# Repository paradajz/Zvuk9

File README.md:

# Zvuk9

Zvuk9 is an expressive USB MIDI controller used to play melodic instruments or drums / samples.

Zvuk9 features:

- 9 pressure and position sensitive pads
- Velocity sensitivity (3 levels of sensitivity and 3 velocity response curves)
- X and Y MIDI assignable to CC (CCs can be the same for all pads or unique per pad)
- X or Y can be set to send pitch bend instead of CC
- Aftertouch (channel or polyphonic)
- 15 programs for storing settings (scale, tonic, split status, X & Y controls, on/off status for notes, aftertouch, and X and Y)
- 7 predefined scales available: natural minor, harmonic minor, melodic minor, major, harmonic major, pentatonic minor, and pentatonic major
- 10 user scales available so you can set which pad will play which note or notes
- Chords can be assigned through user scales, a maximum of 7 notes can be assigned to a pad
- Tonic can be set with Notes buttons
- Notes buttons are illuminated, showing which notes are currently available and which note is currently playing
- By default, tonic goes on Pad1; by using Notes up/down function, all notes can be moved
- Encoder controls for X & Y: CC/Pitch bend, min, max, curve
- Total of 13 response curves available for X and Y
- 4 on/off buttons: notes, X, Y, and aftertouch
- In Split mode, all controls for X and Y, state of 4 on/off buttons, and MIDI channel are unique per pad
- Transport controls: play, stop, and record can be set to MCC, CC, or MCC+CC
- Note off type choice (off channel, on channel/0 velocity)
- All settings saved during reboot
- MIDI over USB and MIDI through 3.5mm mini jack out (cable mini jack to MIDI DIN included)
- Configurable MIDI running status for DIN MIDI
- OLED display

# Compiling

Several compile options are available:

 - Release - Standard firmware with USB MIDI support.
    - Command: `make fw_rls`
 - Debug - Uses LUFA virtual serial mode to print various messages during Zvuk9 usage (USB MIDI is disabled)
    - Command: `make fw_debug`
 - Bootloader - Used to compile bootloader which uses LUFA HID protocol
     - Command: `make boot`

Requirements:

- Linux (tested on Ubuntu 16.04)
- Make
- AVR toolchain
- srec_cat

# Firmware upload

Before uploading Zvuk9 firmware, controller must be put into firmware update mode. To do this, unplug controller from USB, press and hold small button located next to MIDI connector and connect USB cable to PC. After that, PC will recognize Zvuk9 as HID device. Once the bootloader is active, run `hid_bootloader_loader.exe` found under `/bin` directory. This tool will automatically write firwmare to Zvuk9. Make sure `FLASH.hex` is present in directory. Controller will automatically load new firmware once updating is finished.

# Licencing

Zvuk9 uses various modules which are licenced under different licenses. 

- LUFA is licenced under modified MIT licence.
- MIDI module is licenced under MIT.
- U8G2 is licenced under Two-clause BSD licence.
- Core and LESS-DB modules are available under MIT licence.

This project is available under GNU GPLv3 licence. For commerical uses commercial licence is available on demand.

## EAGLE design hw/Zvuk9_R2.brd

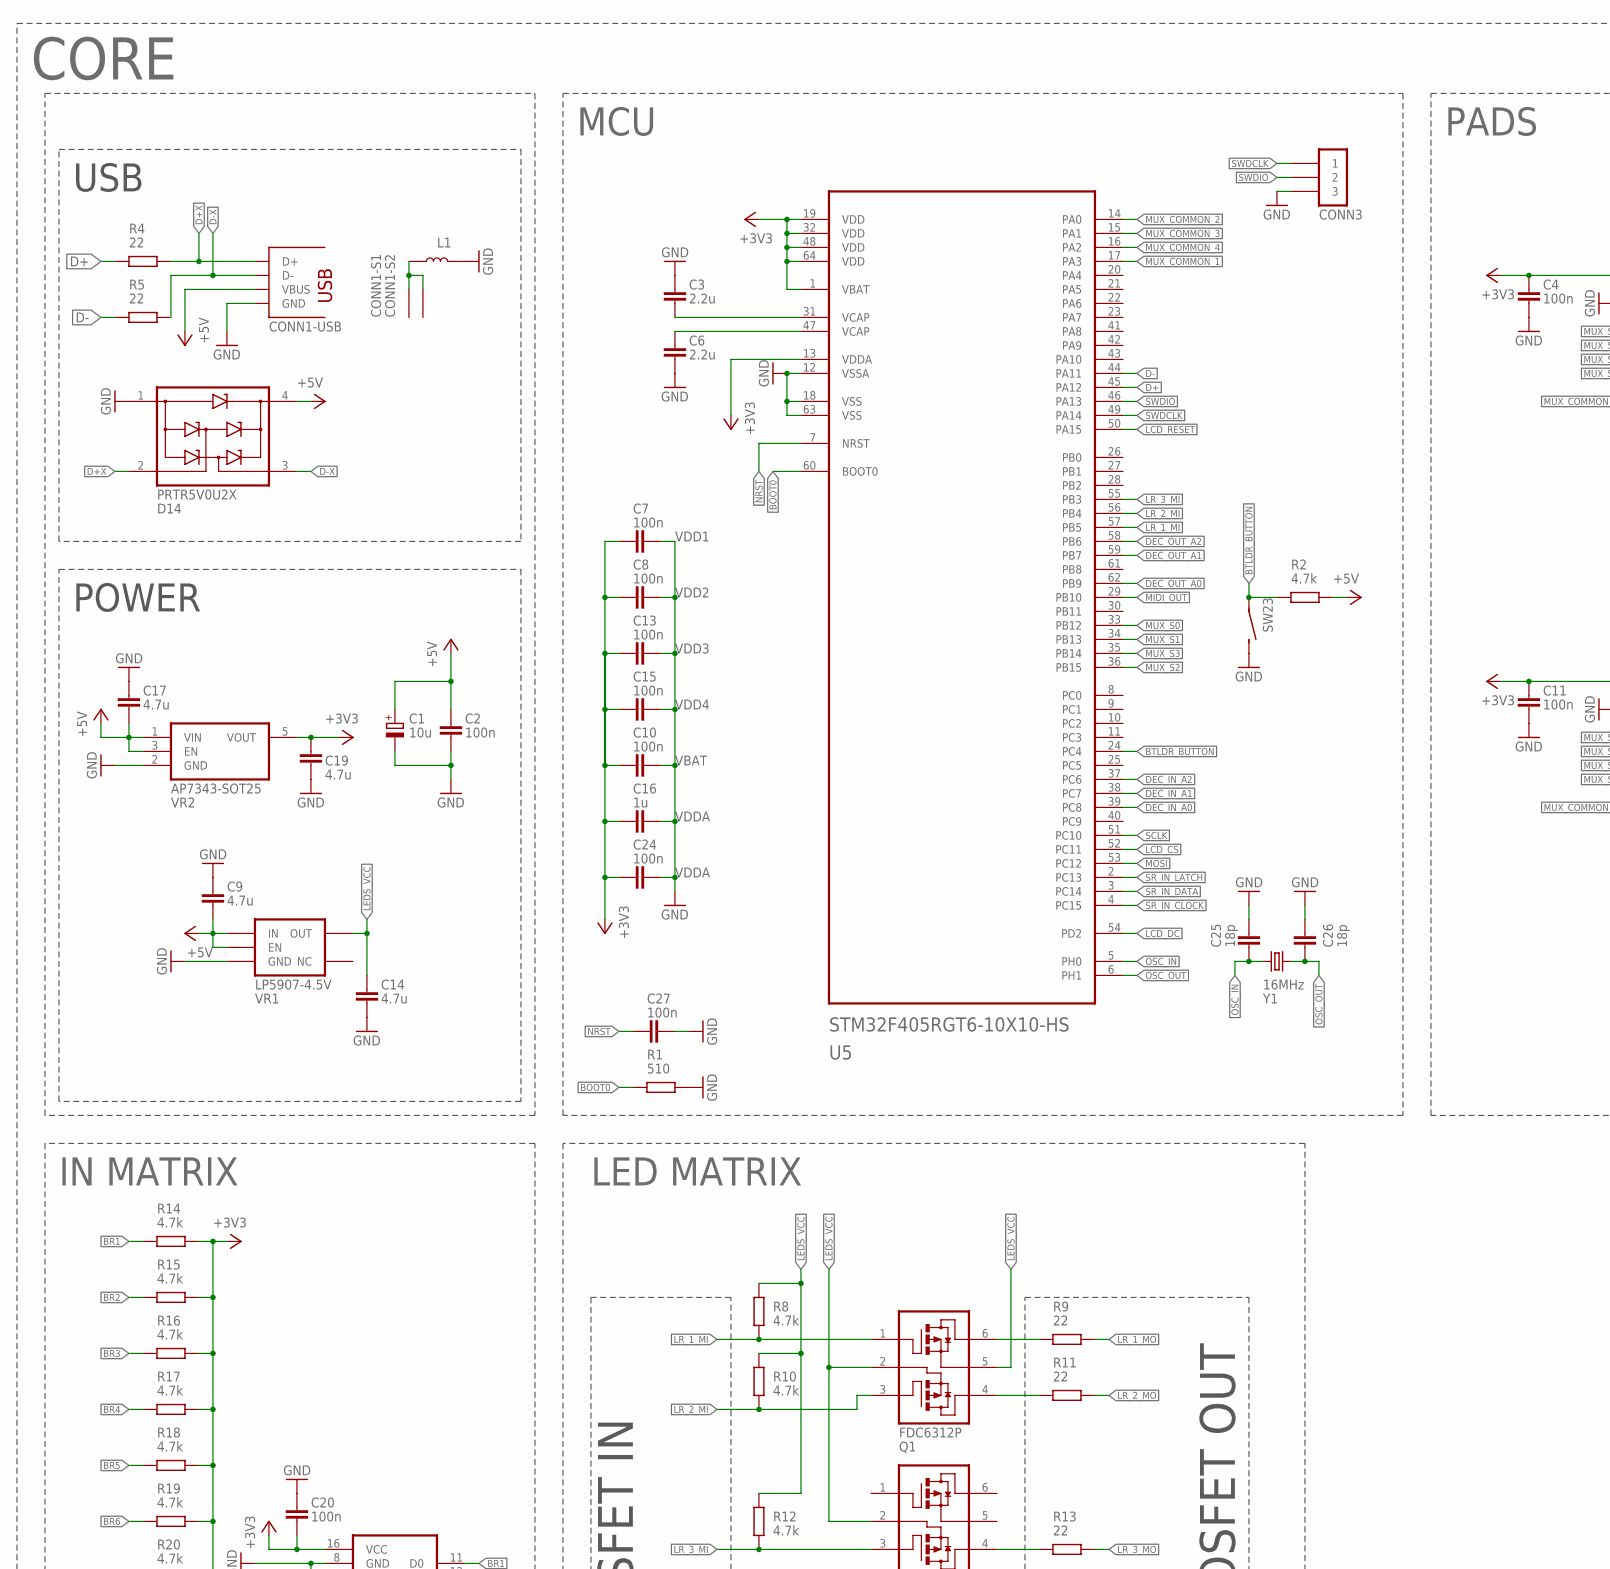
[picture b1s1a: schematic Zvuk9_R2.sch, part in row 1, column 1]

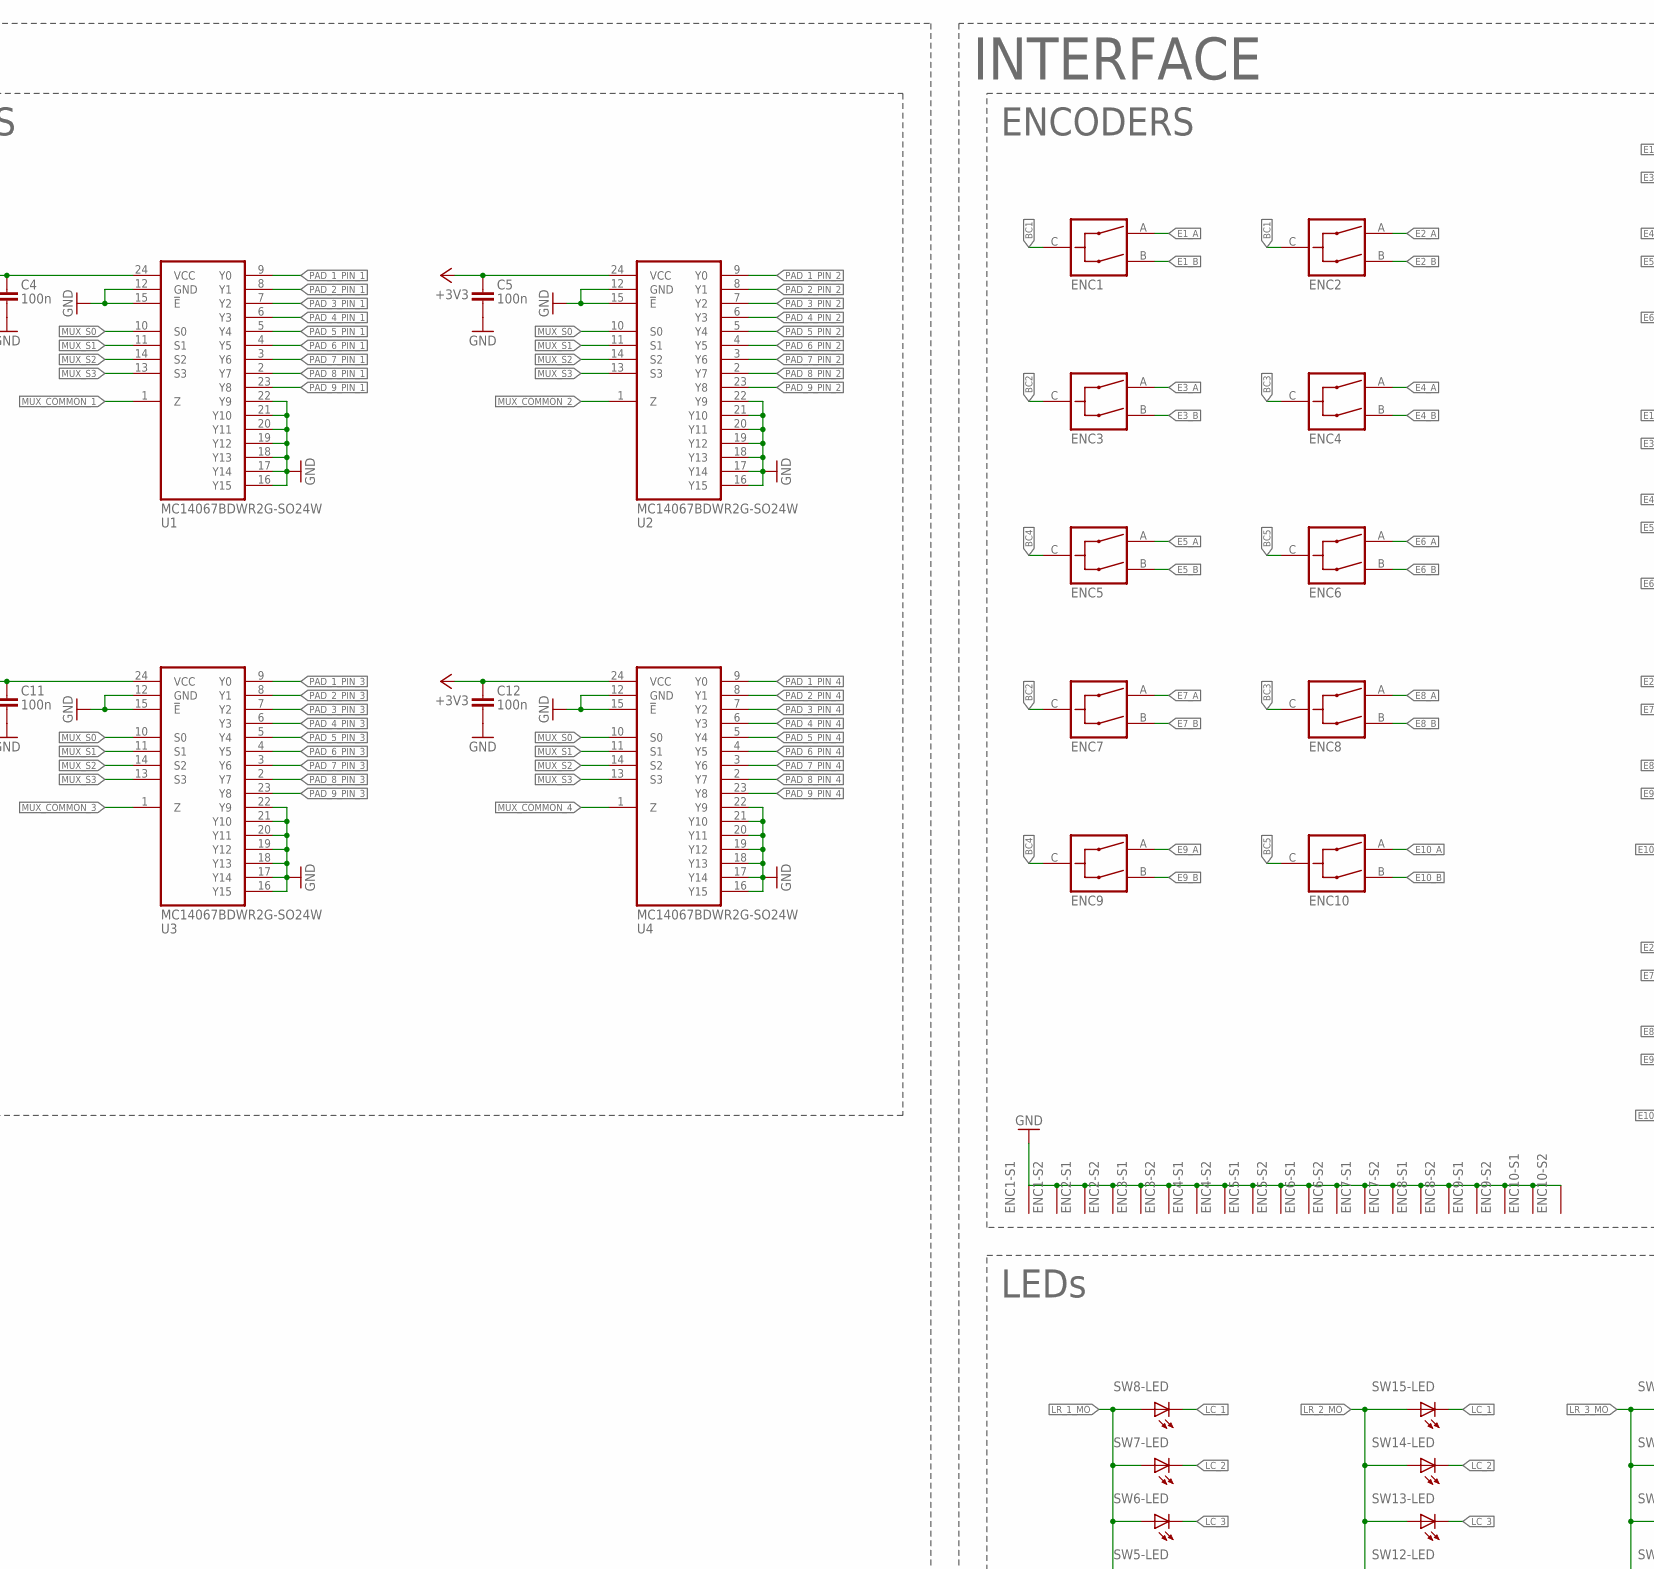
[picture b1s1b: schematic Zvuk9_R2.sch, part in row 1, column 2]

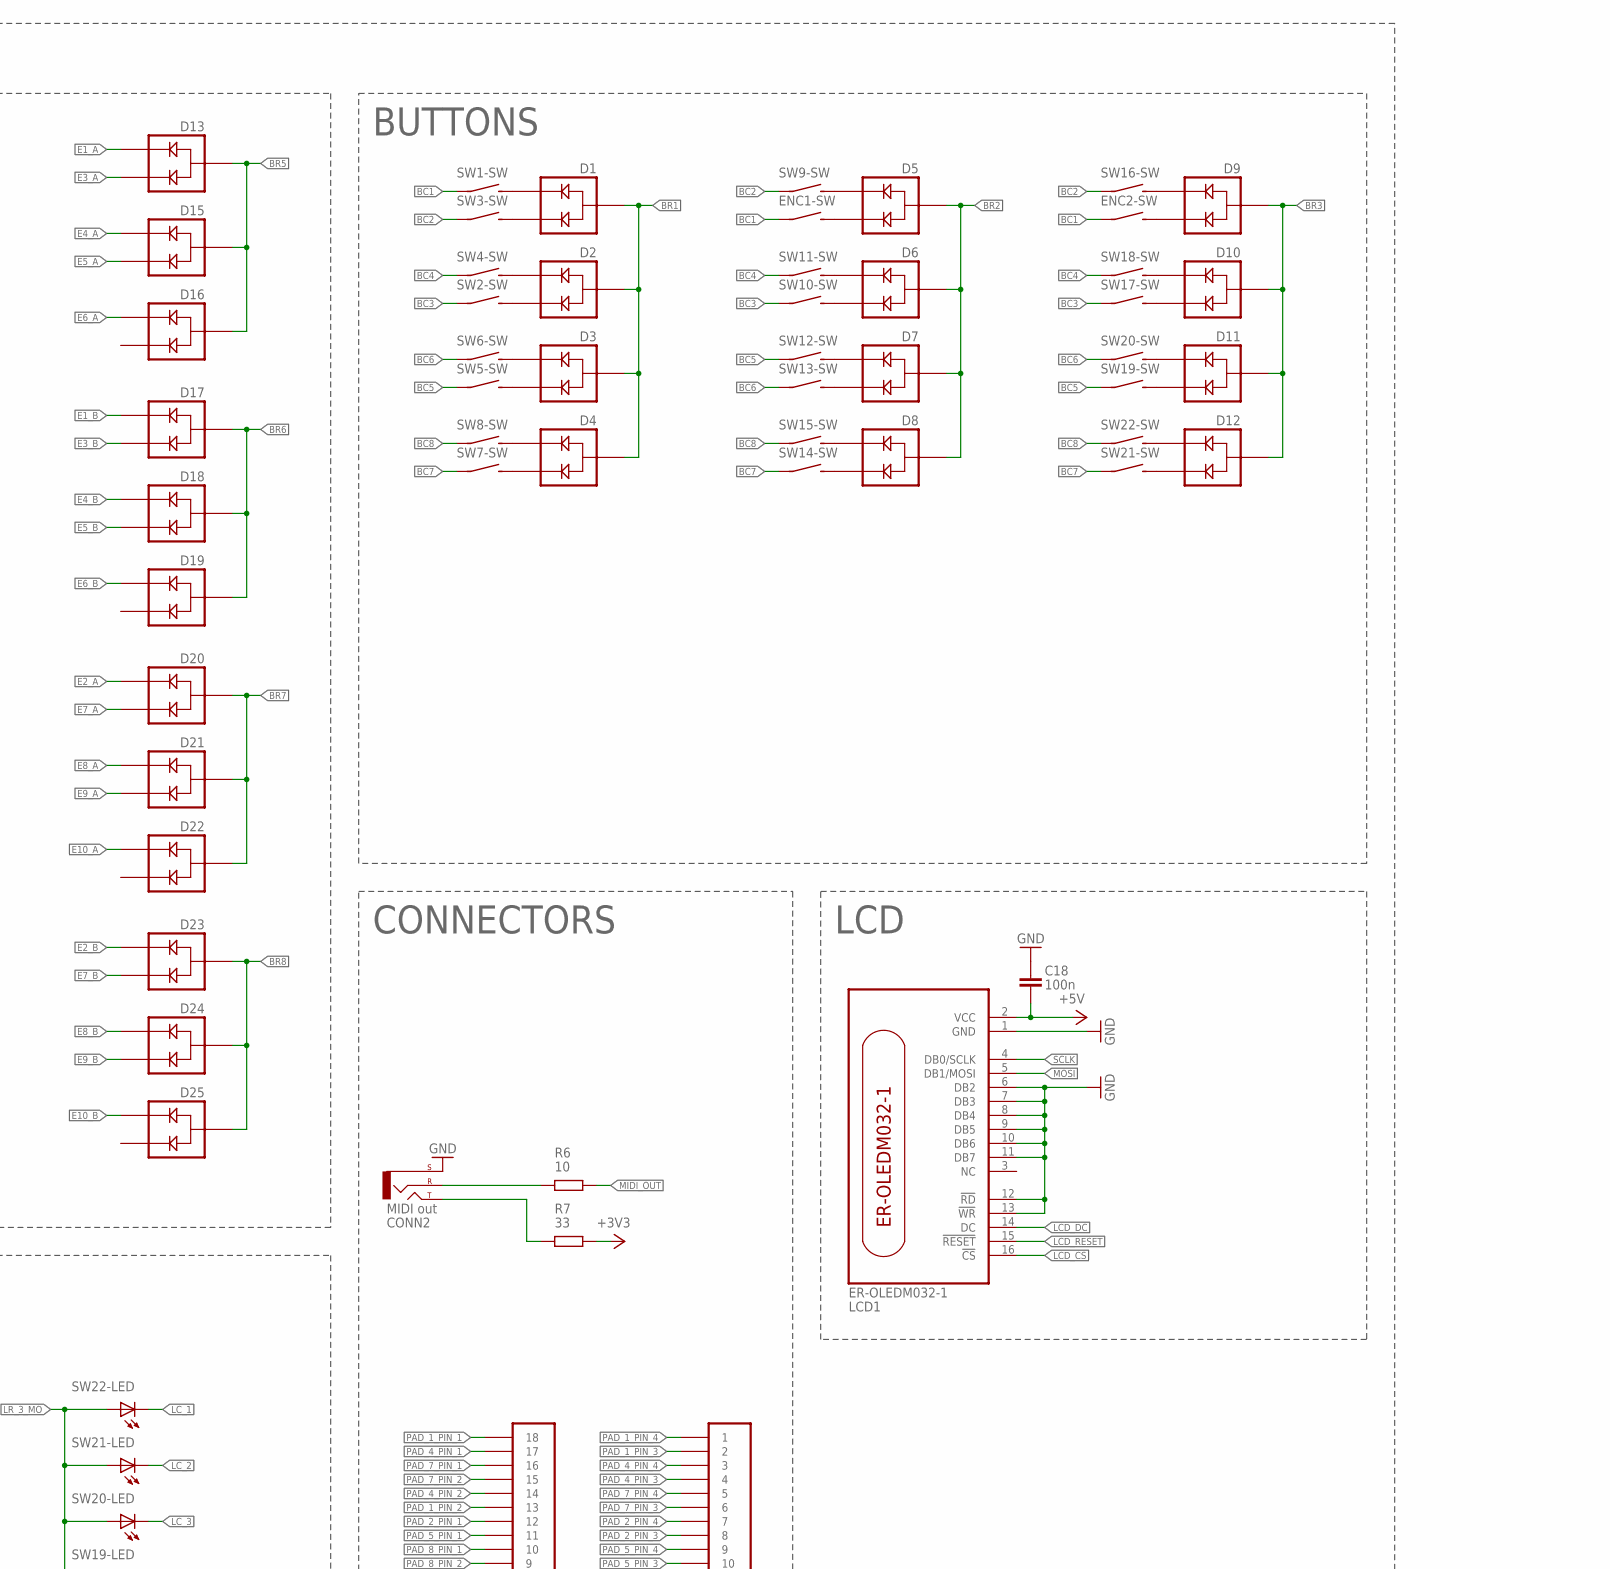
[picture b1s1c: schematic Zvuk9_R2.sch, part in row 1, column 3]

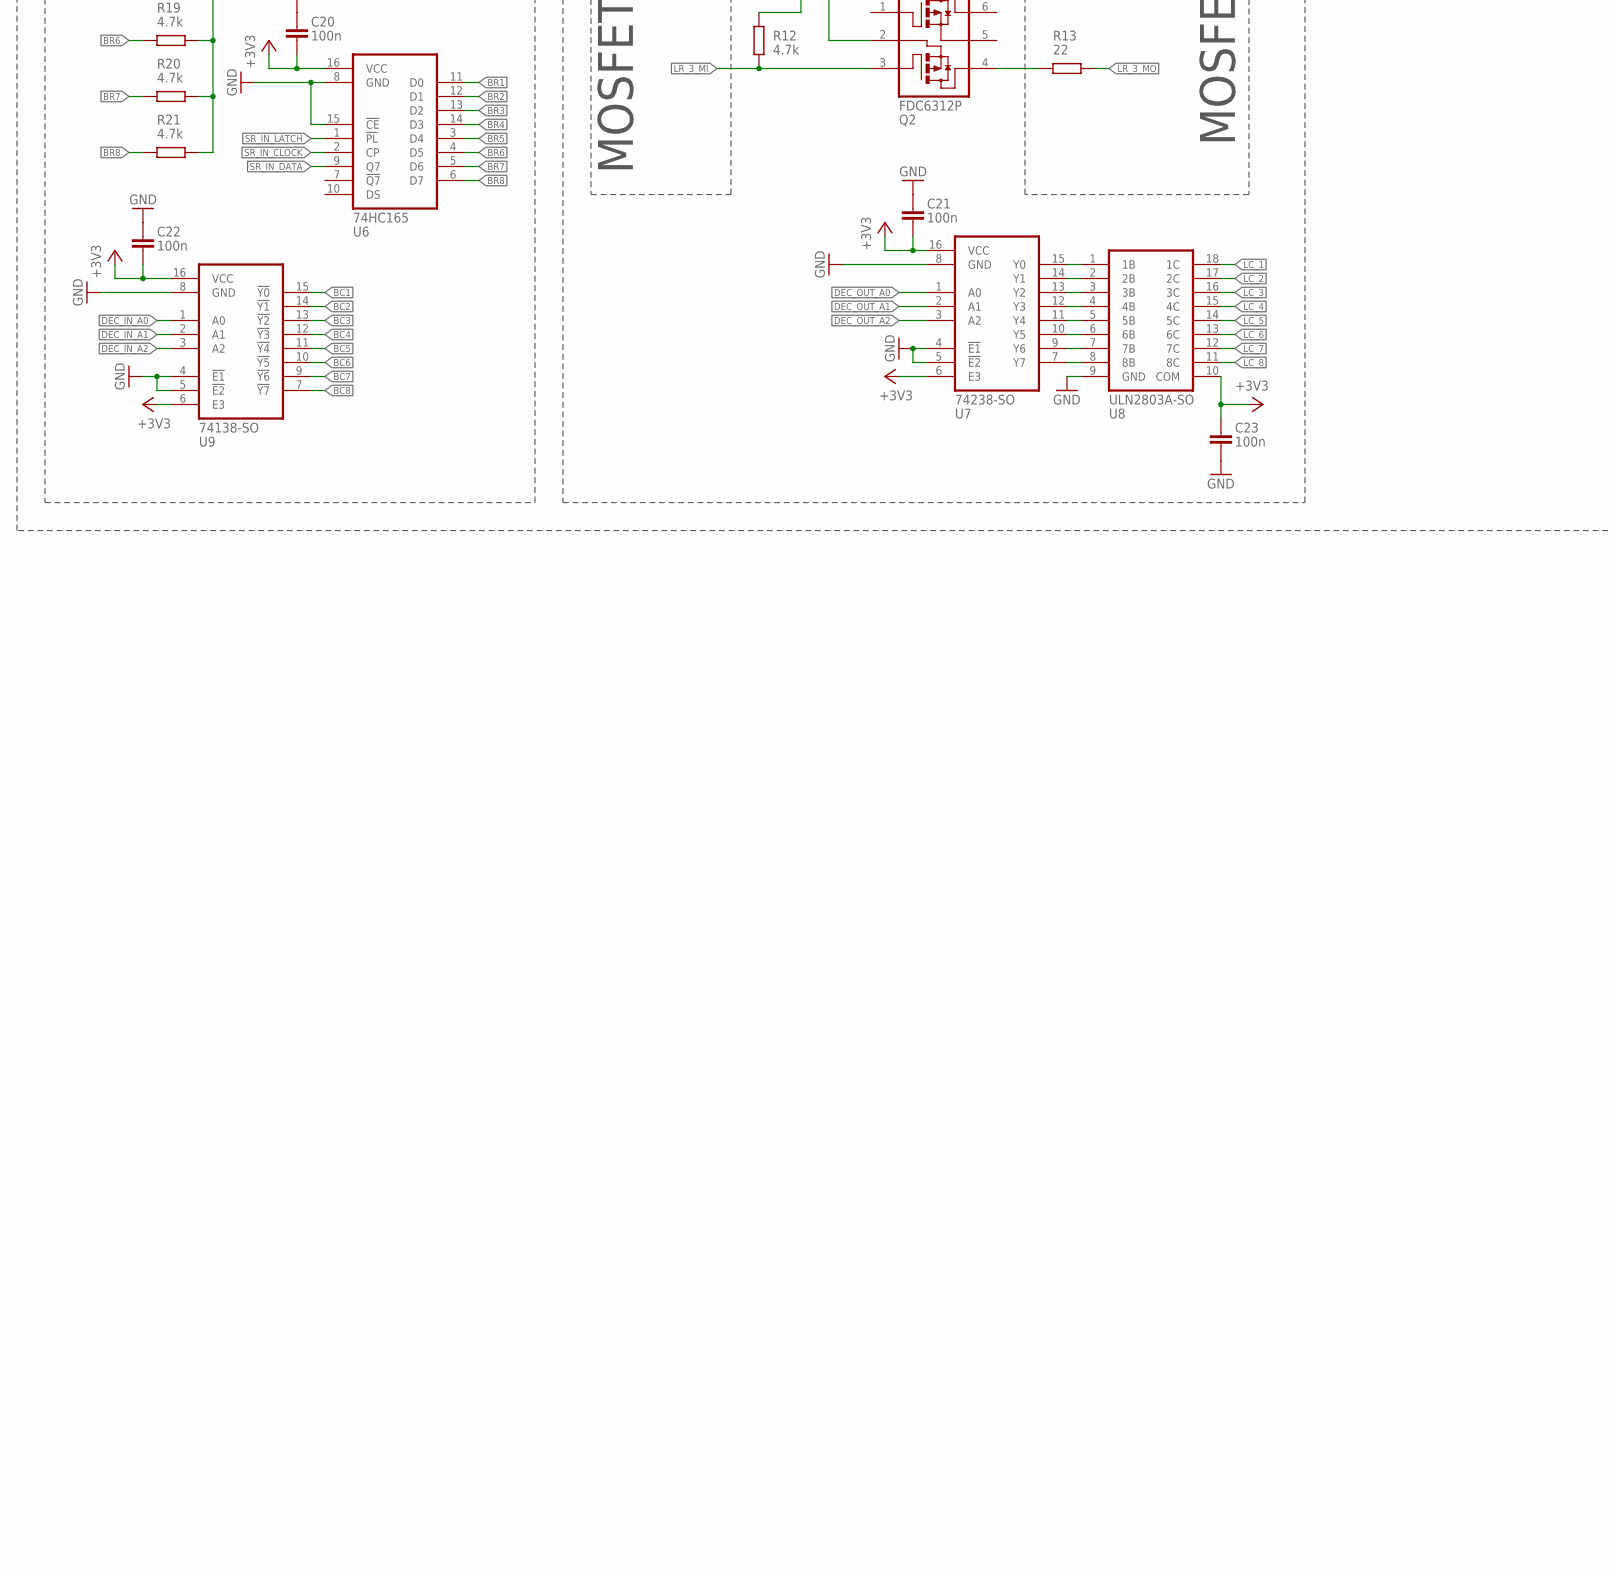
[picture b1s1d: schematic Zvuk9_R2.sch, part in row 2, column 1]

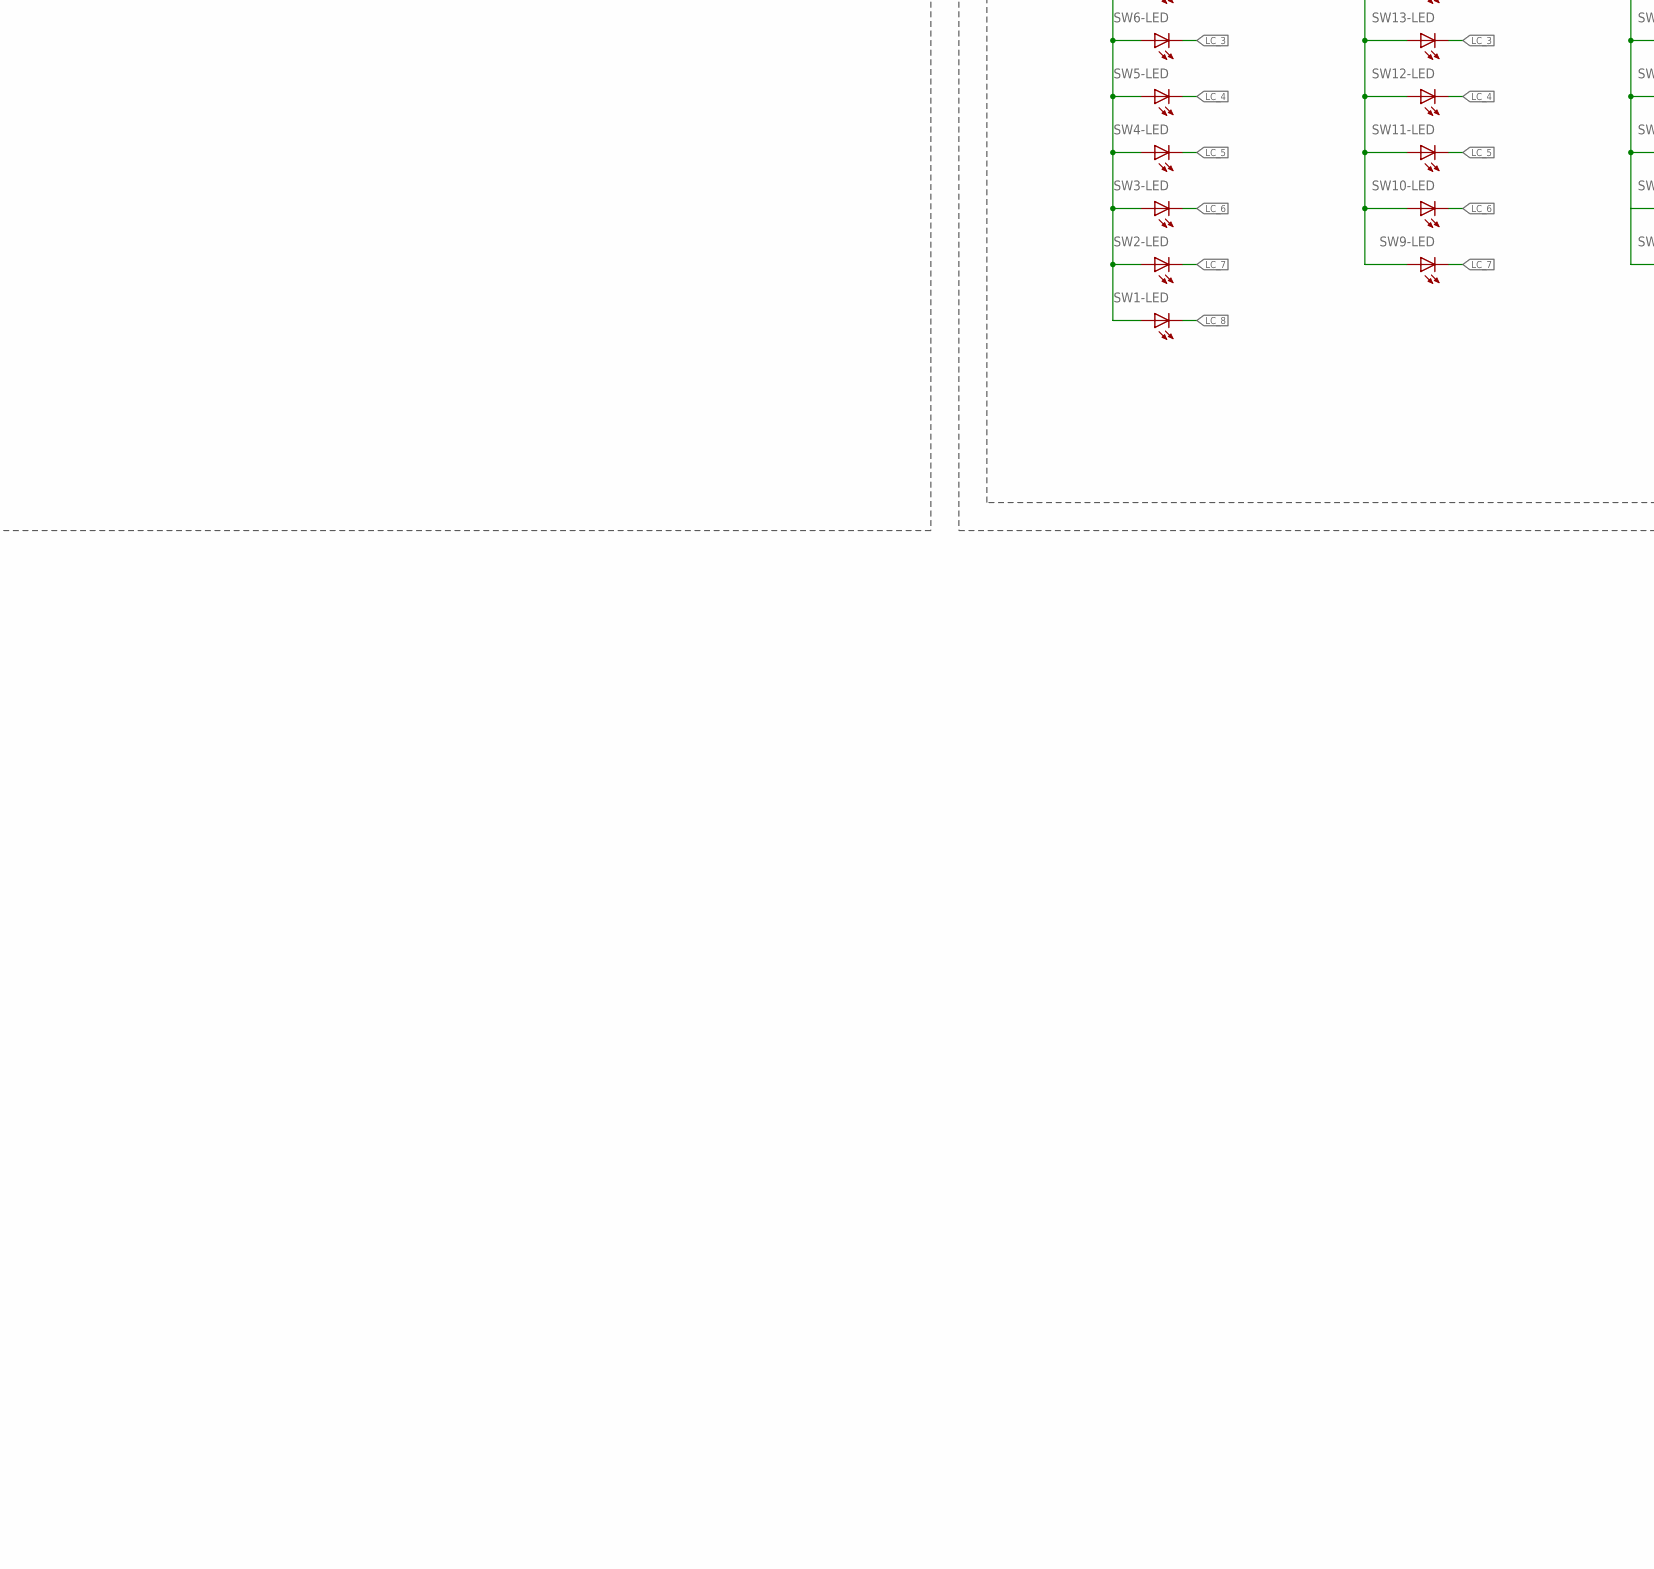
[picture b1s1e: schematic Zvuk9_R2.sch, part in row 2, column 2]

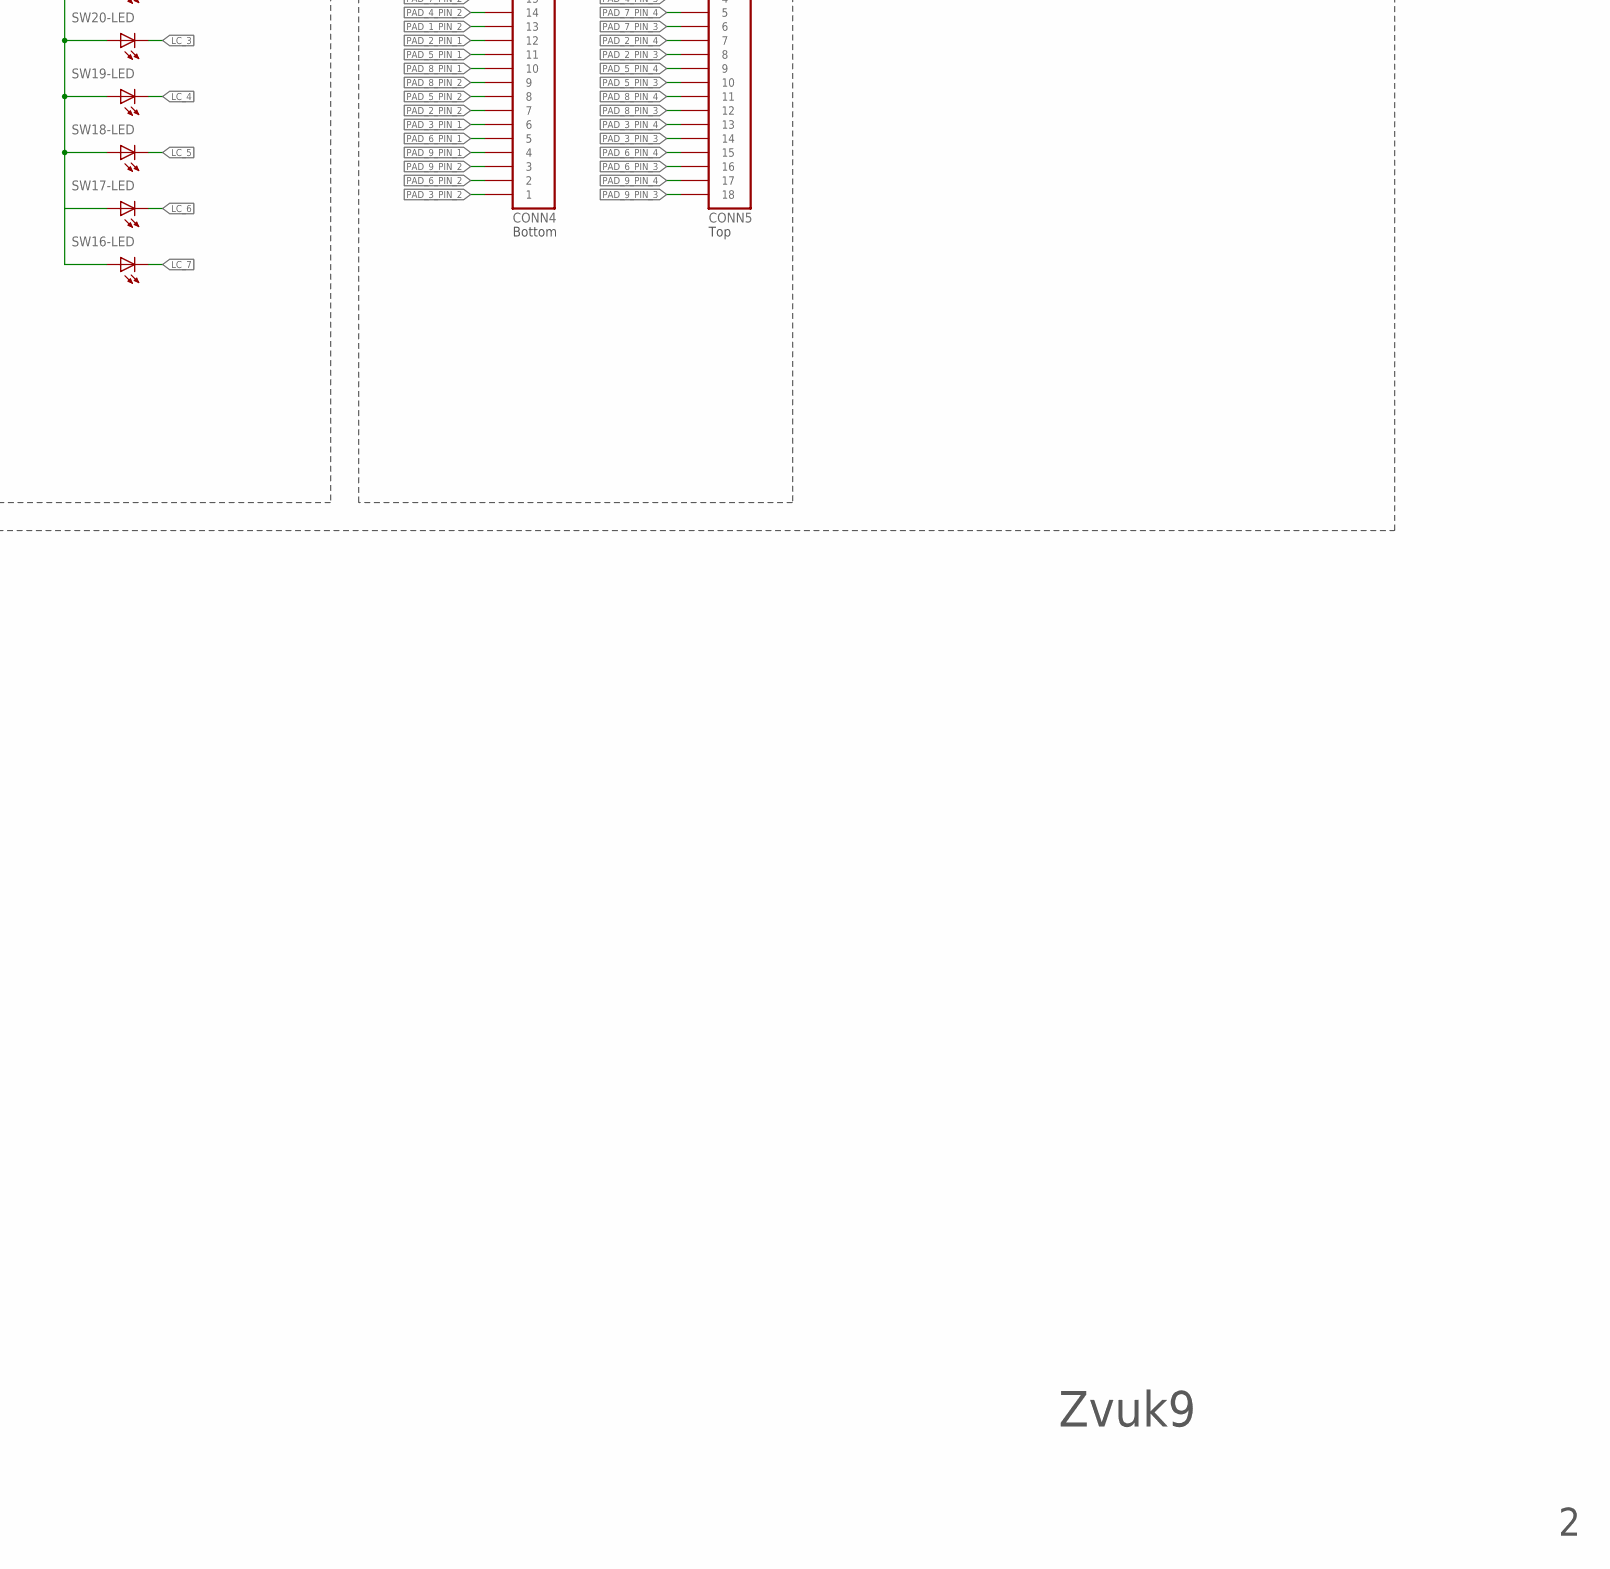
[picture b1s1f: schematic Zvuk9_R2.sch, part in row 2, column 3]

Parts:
C1: 10u; C-TH-E-0502
C2, C4, C5, C7, C8, C10, C11, C12, C13, C15, C18, C20, C21, C22, C23, C24, C27: 100n; C0805
C3, C6: 2.2u; C0805
C9, C14, C17, C19: 4.7u; C0805
C16: 1u; C0805
C25, C26: 18p; C0805
CONN1: USB-B-H; USB-B-PTH
CONN2: MIDI out; SJ1-3523N
CONN3: PINHD-1X03-TH-2.54MM; 1X03-2.54-V
CONN4, CONN5: PINHD-1X18-FFC-SMD-1MM; MOLEX-52271-1879
D1, D2, D3, D4, D5, D6, D7, D8, D9, D10, D11, D12, D13, D15, D16, D17, D18, D19, D20, D21, D22, D23, D24, D25: BAW56; SOT23
D14: PRTR5V0U2X; SOT143
ENC1, ENC2: ALPS-EC12D1524403; ALPS_EC12-SW
ENC3, ENC4, ENC5, ENC6, ENC7, ENC8, ENC9, ENC10: ALPS-EC12E24404AX; EC12E-1
L1: FERRITE_BEAD-BLM21PG221SN1D; L0805
LCD1: ER-OLEDM032-1; ER-OLEDM032-W
Q1, Q2: FDC6312P; SSOT6
R1: 510; R0805
R2, R8, R10, R12, R14, R15, R16, R17, R18, R19, R20, R21: 4.7k; R0805
R4, R5, R9, R11, R13: 22; R0805
R6: 10; R0805
R7: 33; R0805
SW1, SW2, SW3, SW4, SW5, SW6, SW7, SW8, SW9, SW10, SW11, SW12, SW13, SW14, SW15, SW16, SW17, SW18, SW19, SW20, SW21, SW22: OMRON-B3W-9
SW23: SWITCH-B3F; B3F-312X
U1, U2, U3, U4: MC14067BDWR2G-SO24W; SO24-W
U5: STM32F405RGT6-10X10-HS; TQFP-64-10X10-HS
U6: 74HC165; SO16
U7: 74238-SO; SO16
U8: ULN2803A-SO; SO18
U9: 74138-SO; SO16
VR1: LP5907-4.5V; SOT23-5
VR2: AP7343-SOT25; SOT25
Y1: 16MHz; HC49US

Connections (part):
+3V3: C4.1, C5.1, C7.1, C8.1, C10.1, C11.1, C12.1, C13.1, C15.1, C16.1, C19.1, C20.2, C21.2, C22.2, C23.1, C24.1, R7.2, R14.2, R15.2, R16.2, R17.2, R18.2, R19.2, R20.2, R21.2, U1.24 (VCC), U2.24 (VCC), U3.24 (VCC), U4.24 (VCC), U5.1 (VBAT), U5.13 (VDDA), U5.19 (VDD), U5.32 (VDD), U5.48 (VDD), U5.64 (VDD), U6.16 (VCC), U7.6 (E3), U7.16 (VCC), U8.10 (COM), U9.6 (E3), U9.16 (VCC), VR2.5 (VOUT)
+5V: C1.+, C2.1, C9.2, C17.2, C18.2, CONN1.VBUS, D14.4 (VCC), LCD1.2 (VCC), R2.2, VR1.1 (IN), VR1.3 (EN), VR2.1 (VIN), VR2.3 (EN)
BC1: ENC1.C, ENC1.D (1), ENC2.C, ENC2.D (1), SW1.1, U9.15 (!Y0)
BC2: ENC3.C, ENC7.C, SW3.1, SW9.1, SW16.1, U9.14 (!Y1)
BC3: ENC4.C, ENC8.C, SW2.1, SW10.1, SW17.1, U9.13 (!Y2)
BC4: ENC5.C, ENC9.C, SW4.1, SW11.1, SW18.1, U9.12 (!Y3)
BC5: ENC6.C, ENC10.C, SW5.1, SW12.1, SW19.1, U9.11 (!Y4)
BC6: SW6.1, SW13.1, SW20.1, U9.10 (!Y5)
BC7: SW7.1, SW14.1, SW21.1, U9.9 (!Y6)
BC8: SW8.1, SW15.1, SW22.1, U9.7 (!Y7)
BOOT0: R1.1, U5.60 (BOOT0)
BR1: D1.3, D2.3, D3.3, D4.3, R14.1, U6.11 (D0)
BR2: D5.3, D6.3, D7.3, D8.3, R15.1, U6.12 (D1)
BR3: D9.3, D10.3, D11.3, D12.3, R16.1, U6.13 (D2)
BR4: R17.1, U6.14 (D3)
BR5: D13.3, D15.3, D16.3, R18.1, U6.3 (D4)
BR6: D17.3, D18.3, D19.3, R19.1, U6.4 (D5)
BR7: D20.3, D21.3, D22.3, R20.1, U6.5 (D6)
BR8: D23.3, D24.3, D25.3, R21.1, U6.6 (D7)
BTLDR_BUTTON: R2.1, SW23.1, U5.24 (PC4)
D+: R4.1, U5.45 (PA12)
D+X: CONN1.D+, D14.2 (I/O1), R4.2
D-: R5.1, U5.44 (PA11)
D-X: CONN1.D-, D14.3 (I/O2), R5.2
DEC_IN_A0: U5.39 (PC8), U9.1 (A0)
DEC_IN_A1: U5.38 (PC7), U9.2 (A1)
DEC_IN_A2: U5.37 (PC6), U9.3 (A2)
DEC_OUT_A0: U5.62 (PB9), U7.1 (A0)
DEC_OUT_A1: U5.59 (PB7), U7.2 (A1)
DEC_OUT_A2: U5.58 (PB6), U7.3 (A2)
E1_A: D13.1, ENC1.A
E1_B: D17.1, ENC1.B
E2_A: D20.1, ENC2.A
E2_B: D23.1, ENC2.B
E3_A: D13.2, ENC3.A
E3_B: D17.2, ENC3.B
E4_A: D15.1, ENC4.A
E4_B: D18.1, ENC4.B
E5_A: D15.2, ENC5.A
E5_B: D18.2, ENC5.B
E6_A: D16.1, ENC6.A
E6_B: D19.1, ENC6.B
E7_A: D20.2, ENC7.A
E7_B: D23.2, ENC7.B
E8_A: D21.1, ENC8.A
E8_B: D24.1, ENC8.B
E9_A: D21.2, ENC9.A
E9_B: D24.2, ENC9.B
E10_A: D22.1, ENC10.A
E10_B: D25.1, ENC10.B
GND: C1.-, C2.2, C3.1, C4.2, C5.2, C6.2, C7.2, C8.2, C9.1, C10.2, C11.2, C12.2, C13.2, C14.2, C15.2, C16.2, C17.1, C18.1, C19.2, C20.1, C21.1, C22.1, C23.2, C24.2, C25.2, C26.2, C27.2, CONN1.GND, CONN2.1 (SLEEVE), CONN3.3, D14.1 (GND), ENC1.S1 (S), ENC1.S2 (S), ENC2.S1 (S), ENC2.S2 (S), ENC3.S1 (S), ENC3.S2 (S), ENC4.S1 (S), ENC4.S2 (S), ENC5.S1 (S), ENC5.S2 (S), ENC6.S1 (S), ENC6.S2 (S), ENC7.S1 (S), ENC7.S2 (S), ENC8.S1 (S), ENC8.S2 (S), ENC9.S1 (S), ENC9.S2 (S), ENC10.S1 (S), ENC10.S2 (S), L1.2, LCD1.1 (GND), LCD1.6 (DB2), LCD1.7 (DB3), LCD1.8 (DB4), LCD1.9 (DB5), LCD1.10 (DB6), LCD1.11 (DB7), LCD1.12 (!RD), LCD1.13 (!WR), R1.2, SW23.2, U1.12 (GND), U1.15 (!E), U1.16 (Y15), U1.17 (Y14), U1.18 (Y13), U1.19 (Y12), U1.20 (Y11), U1.21 (Y10), U1.22 (Y9), U2.12 (GND), U2.15 (!E), U2.16 (Y15), U2.17 (Y14), U2.18 (Y13), U2.19 (Y12), U2.20 (Y11), U2.21 (Y10)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
LCD_CS: LCD1.16 (!CS), U5.52 (PC11)
LCD_DC: LCD1.14 (DC), U5.54 (PD2)
LCD_RESET: LCD1.15 (!RESET), U5.50 (PA15)
LC_1: SW8.6-C (C), SW15.6-C (C), SW22.6-C (C), U8.18 (1C)
LC_2: SW7.6-C (C), SW14.6-C (C), SW21.6-C (C), U8.17 (2C)
LC_3: SW6.6-C (C), SW13.6-C (C), SW20.6-C (C), U8.16 (3C)
LC_4: SW5.6-C (C), SW12.6-C (C), SW19.6-C (C), U8.15 (4C)
LC_5: SW4.6-C (C), SW11.6-C (C), SW18.6-C (C), U8.14 (5C)
LC_6: SW3.6-C (C), SW10.6-C (C), SW17.6-C (C), U8.13 (6C)
LC_7: SW2.6-C (C), SW9.6-C (C), SW16.6-C (C), U8.12 (7C)
LC_8: SW1.6-C (C), U8.11 (8C)
LEDS_VCC: C14.1, Q1.2 (S2), Q1.5 (S1), Q2.2 (S2), R8.1, R10.1, R12.1, VR1.5 (OUT)
LR_1_MI: Q1.1 (G1), R8.2, U5.57 (PB5)
LR_1_MO: R9.2, SW1.6-A (A), SW2.6-A (A), SW3.6-A (A), SW4.6-A (A), SW5.6-A (A), SW6.6-A (A), SW7.6-A (A), SW8.6-A (A)
LR_2_MI: Q1.3 (G2), R10.2, U5.56 (PB4)
LR_2_MO: R11.2, SW9.6-A (A), SW10.6-A (A), SW11.6-A (A), SW12.6-A (A), SW13.6-A (A), SW14.6-A (A), SW15.6-A (A)
LR_3_MI: Q2.3 (G2), R12.2, U5.55 (PB3)
LR_3_MO: R13.2, SW16.6-A (A), SW17.6-A (A), SW18.6-A (A), SW19.6-A (A), SW20.6-A (A), SW21.6-A (A), SW22.6-A (A)
MIDI_OUT: R6.2, U5.29 (PB10)
MOSI: LCD1.5 (DB1/MOSI), U5.53 (PC12)
MUX_COMMON_1: U1.1 (Z), U5.17 (PA3)
MUX_COMMON_2: U2.1 (Z), U5.14 (PA0)
MUX_COMMON_3: U3.1 (Z), U5.15 (PA1)
MUX_COMMON_4: U4.1 (Z), U5.16 (PA2)
MUX_S0: U1.10 (S0), U2.10 (S0), U3.10 (S0), U4.10 (S0), U5.33 (PB12)
MUX_S1: U1.11 (S1), U2.11 (S1), U3.11 (S1), U4.11 (S1), U5.34 (PB13)
MUX_S2: U1.14 (S2), U2.14 (S2), U3.14 (S2), U4.14 (S2), U5.36 (PB15)
MUX_S3: U1.13 (S3), U2.13 (S3), U3.13 (S3), U4.13 (S3), U5.35 (PB14)
unnamed: U7.15 (Y0), U8.1 (1B)
unnamed: U7.14 (Y1), U8.2 (2B)
unnamed: U7.13 (Y2), U8.3 (3B)
unnamed: U7.12 (Y3), U8.4 (4B)
unnamed: D1.1, SW1.3 (2)
unnamed: D2.2, SW2.3 (2)
unnamed: CONN2.2 (TIP), R7.1
unnamed: D2.1, SW4.3 (2)
unnamed: D1.2, SW3.3 (2)
unnamed: D3.2, SW5.3 (2)
unnamed: D3.1, SW6.3 (2)
unnamed: C3.2, U5.31 (VCAP)
unnamed: C6.1, U5.47 (VCAP)
unnamed: D4.2, SW7.3 (2)
unnamed: D4.1, SW8.3 (2)
unnamed: D5.2, ENC1.E (2)
unnamed: D6.2, SW10.3 (2)
unnamed: D6.1, SW11.3 (2)
unnamed: D7.1, SW12.3 (2)
unnamed: D7.2, SW13.3 (2)
unnamed: D8.2, SW14.3 (2)
unnamed: D8.1, SW15.3 (2)
unnamed: D5.1, SW9.3 (2)
unnamed: D9.2, ENC2.E (2)
unnamed: D9.1, SW16.3 (2)
unnamed: D10.2, SW17.3 (2)
unnamed: D10.1, SW18.3 (2)
unnamed: D11.2, SW19.3 (2)
unnamed: D11.1, SW20.3 (2)
unnamed: D12.2, SW21.3 (2)
unnamed: D12.1, SW22.3 (2)
unnamed: CONN2.3 (RING), R6.1
unnamed: U7.11 (Y4), U8.5 (5B)
unnamed: U7.10 (Y5), U8.6 (6B)
unnamed: U7.9 (Y6), U8.7 (7B)
unnamed: U7.7 (Y7), U8.8 (8B)
unnamed: Q1.6 (D1), R9.1
unnamed: Q1.4 (D2), R11.1
unnamed: Q2.4 (D2), R13.1
NRST: C27.1, U5.7 (NRST)
OSC_IN: C25.1, U5.5 (PH0), Y1.1
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
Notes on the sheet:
LCD
BUTTONS
ENCODERS
CONNECTORS
Zvuk9
LEDs
USB
MOSFET IN
MOSFET OUT
MCU
POWER
IN MATRIX
LED MATRIX
CORE
INTERFACE
PADS
Bottom
Top
VBAT
VDD1
VDD2
VDD3
VDD4
VDDA

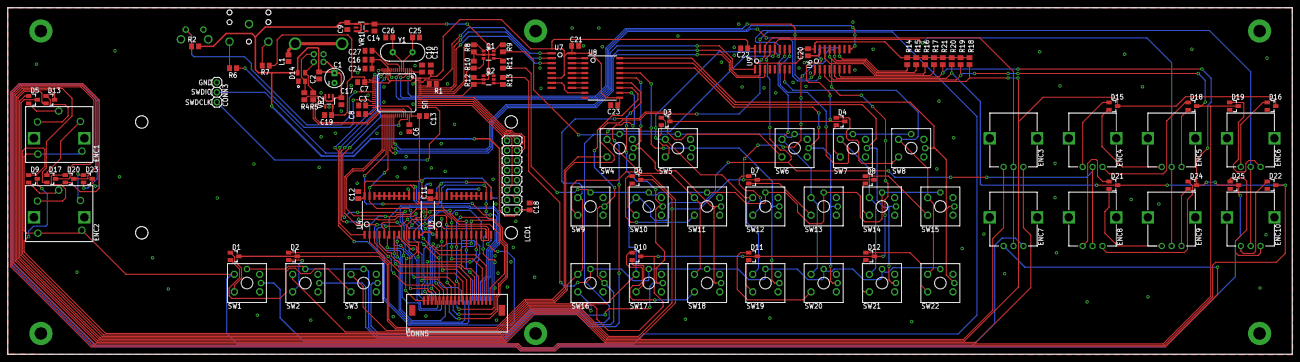
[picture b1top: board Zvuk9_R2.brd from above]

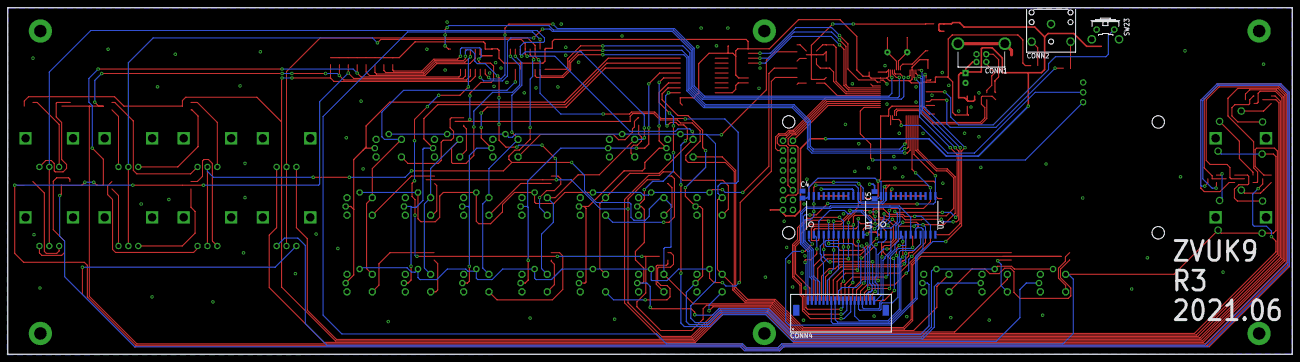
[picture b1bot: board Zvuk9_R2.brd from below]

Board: 2 copper layers, 330.1 x 89.0 mm, 126 parts (8 on the bottom side), 164 nets.

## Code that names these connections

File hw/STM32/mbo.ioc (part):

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Mcu.Name=STM32F410C(8-B)Tx
Mcu.Package=LQFP48
Mcu.UserName=STM32F410CBTx
PA0-WKUP.GPIOParameters=GPIO_Label
PA0-WKUP.GPIO_Label=LED_COL_DEC_1
PA0-WKUP.Signal=GPIO_Output
PA1.GPIOParameters=GPIO_Label
PA1.GPIO_Label=LED_COL_DEC_2
PA1.Signal=GPIO_Output
PA10.Mode=Asynchronous
PA10.Signal=USART1_RX
PA11.GPIOParameters=GPIO_Label
PA11.GPIO_Label=IN_MATRIX_COL_S2
PA11.Signal=GPIO_Output
PA12.GPIOParameters=GPIO_Label
PA12.GPIO_Label=IN_MATRIX_COL_S1
PA12.Signal=GPIO_Output
PA13.Mode=Serial_Wire
PA13.Signal=SYS_JTMS-SWDIO
PA14.Mode=Serial_Wire
PA14.Signal=SYS_JTCK-SWCLK
PA15.GPIOParameters=GPIO_Label
PA15.GPIO_Label=DISPLAY NSS
PA15.Mode=NSS_Signal_Hard_Output
PA15.Signal=SPI1_NSS
PA2.GPIOParameters=GPIO_Label
PA2.GPIO_Label=LED_COL_DEC_3
PA2.Signal=GPIO_Output
PA3.GPIOParameters=GPIO_Label
PA3.GPIO_Label=MUX COMMON 1
PA3.Signal=ADCx_IN3
PA4.GPIOParameters=GPIO_Label
PA4.GPIO_Label=MUX COMMON 2
PA4.Signal=ADCx_IN4
PA5.GPIOParameters=GPIO_Label
PA5.GPIO_Label=MUX COMMON 3
PA5.Signal=ADCx_IN5
PA6.GPIOParameters=GPIO_Label
PA6.GPIO_Label=MUX COMMON 4
PA6.Signal=ADCx_IN6
PA7.GPIOParameters=GPIO_Label
PA7.GPIO_Label=MUX S0
PA7.Signal=GPIO_Output
PA8.GPIOParameters=GPIO_Label
PA8.GPIO_Label=IN_MATRIX_COL_S0
PA8.Signal=GPIO_Output
PA9.Mode=Asynchronous
PA9.Signal=USART1_TX
PB0.GPIOParameters=GPIO_Label
PB0.GPIO_Label=MUX S1
PB0.Signal=GPIO_Output
PB1.GPIOParameters=GPIO_Label
PB1.GPIO_Label=MUX S2
PB1.Signal=GPIO_Output
PB12.GPIOParameters=GPIO_Label
PB12.GPIO_Label=IN_REG_LATCH
PB12.Signal=GPIO_Output
PB13.GPIOParameters=GPIO_Label
PB13.GPIO_Label=IN_REG_CLK
PB13.Mode=RX_Only_Simplex_Unidirect_Master
PB13.Signal=SPI2_SCK
PB14.GPIOParameters=GPIO_Label
PB14.GPIO_Label=IN_REG_DATA
PB14.Mode=RX_Only_Simplex_Unidirect_Master
PB14.Signal=SPI2_MISO
PB2.GPIOParameters=GPIO_Label
PB2.GPIO_Label=MUX S3
PB2.Signal=GPIO_Output
PB3.GPIOParameters=GPIO_Label
PB3.GPIO_Label=DISPLAY SCLK
PB3.Mode=TX_Only_Simplex_Unidirect_Master
PB3.Signal=SPI1_SCK
PB4.GPIOParameters=GPIO_Label
PB4.GPIO_Label=DISPLAY DC
PB4.Signal=GPIO_Output
PB5.GPIOParameters=GPIO_Label
PB5.GPIO_Label=DISPLAY MOSI
PB5.Mode=TX_Only_Simplex_Unidirect_Master
PB5.Signal=SPI1_MOSI
PB6.GPIOParameters=GPIO_Label
PB6.GPIO_Label=BTLDR_IN
PB6.Signal=GPIO_Input
PB7.GPIOParameters=GPIO_Label
PB7.GPIO_Label=STATUS_LED_2
PB7.Signal=GPIO_Input
PB8.GPIOParameters=GPIO_Label
PB8.GPIO_Label=STATUS_LED_1
PB8.Signal=GPIO_Output
PC13-ANTI_TAMP.GPIOParameters=GPIO_Label
PC13-ANTI_TAMP.GPIO_Label=LED ROW 1
PC13-ANTI_TAMP.Signal=GPIO_Output
PC14-OSC32_IN.GPIOParameters=GPIO_Label
PC14-OSC32_IN.GPIO_Label=LED ROW 2
PC14-OSC32_IN.Signal=GPIO_Output
PC15-OSC32_OUT.GPIOParameters=GPIO_Label
PC15-OSC32_OUT.GPIO_Label=LED_ROW_3
PC15-OSC32_OUT.Signal=GPIO_Output
PH0\ -\ OSC_IN.Mode=HSE-External-Oscillator
PH0\ -\ OSC_IN.Signal=RCC_OSC_IN
PH1\ -\ OSC_OUT.Mode=HSE-External-Oscillator
PH1\ -\ OSC_OUT.Signal=RCC_OSC_OUT
RCC.HSE_VALUE=25000000
RCC.SYSCLKFreq_VALUE=16000000
